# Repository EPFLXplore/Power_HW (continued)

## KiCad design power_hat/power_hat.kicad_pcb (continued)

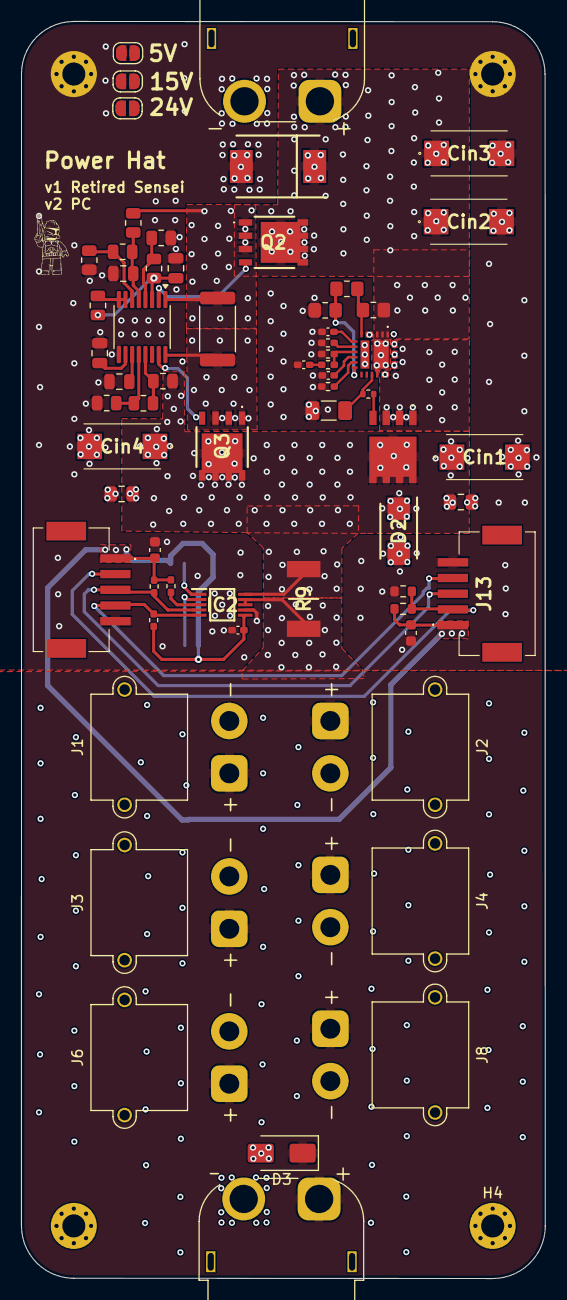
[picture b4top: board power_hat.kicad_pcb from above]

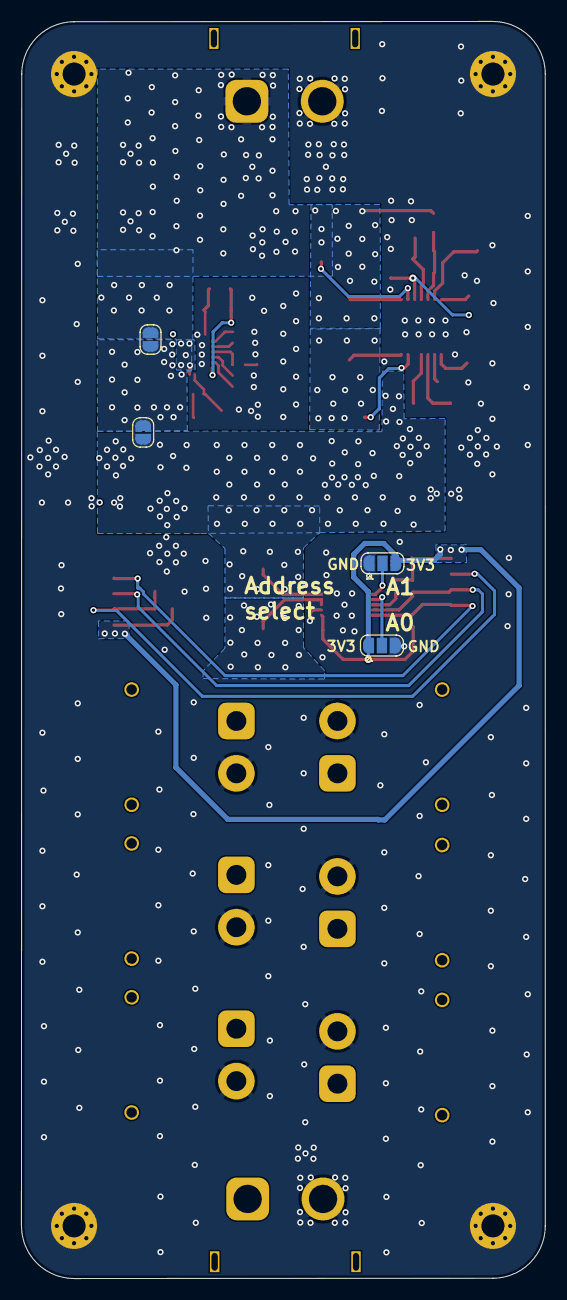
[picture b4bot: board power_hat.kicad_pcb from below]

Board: 4 copper layers, 50.0 x 120.0 mm, 71 parts (4 on the bottom side), 35 nets.

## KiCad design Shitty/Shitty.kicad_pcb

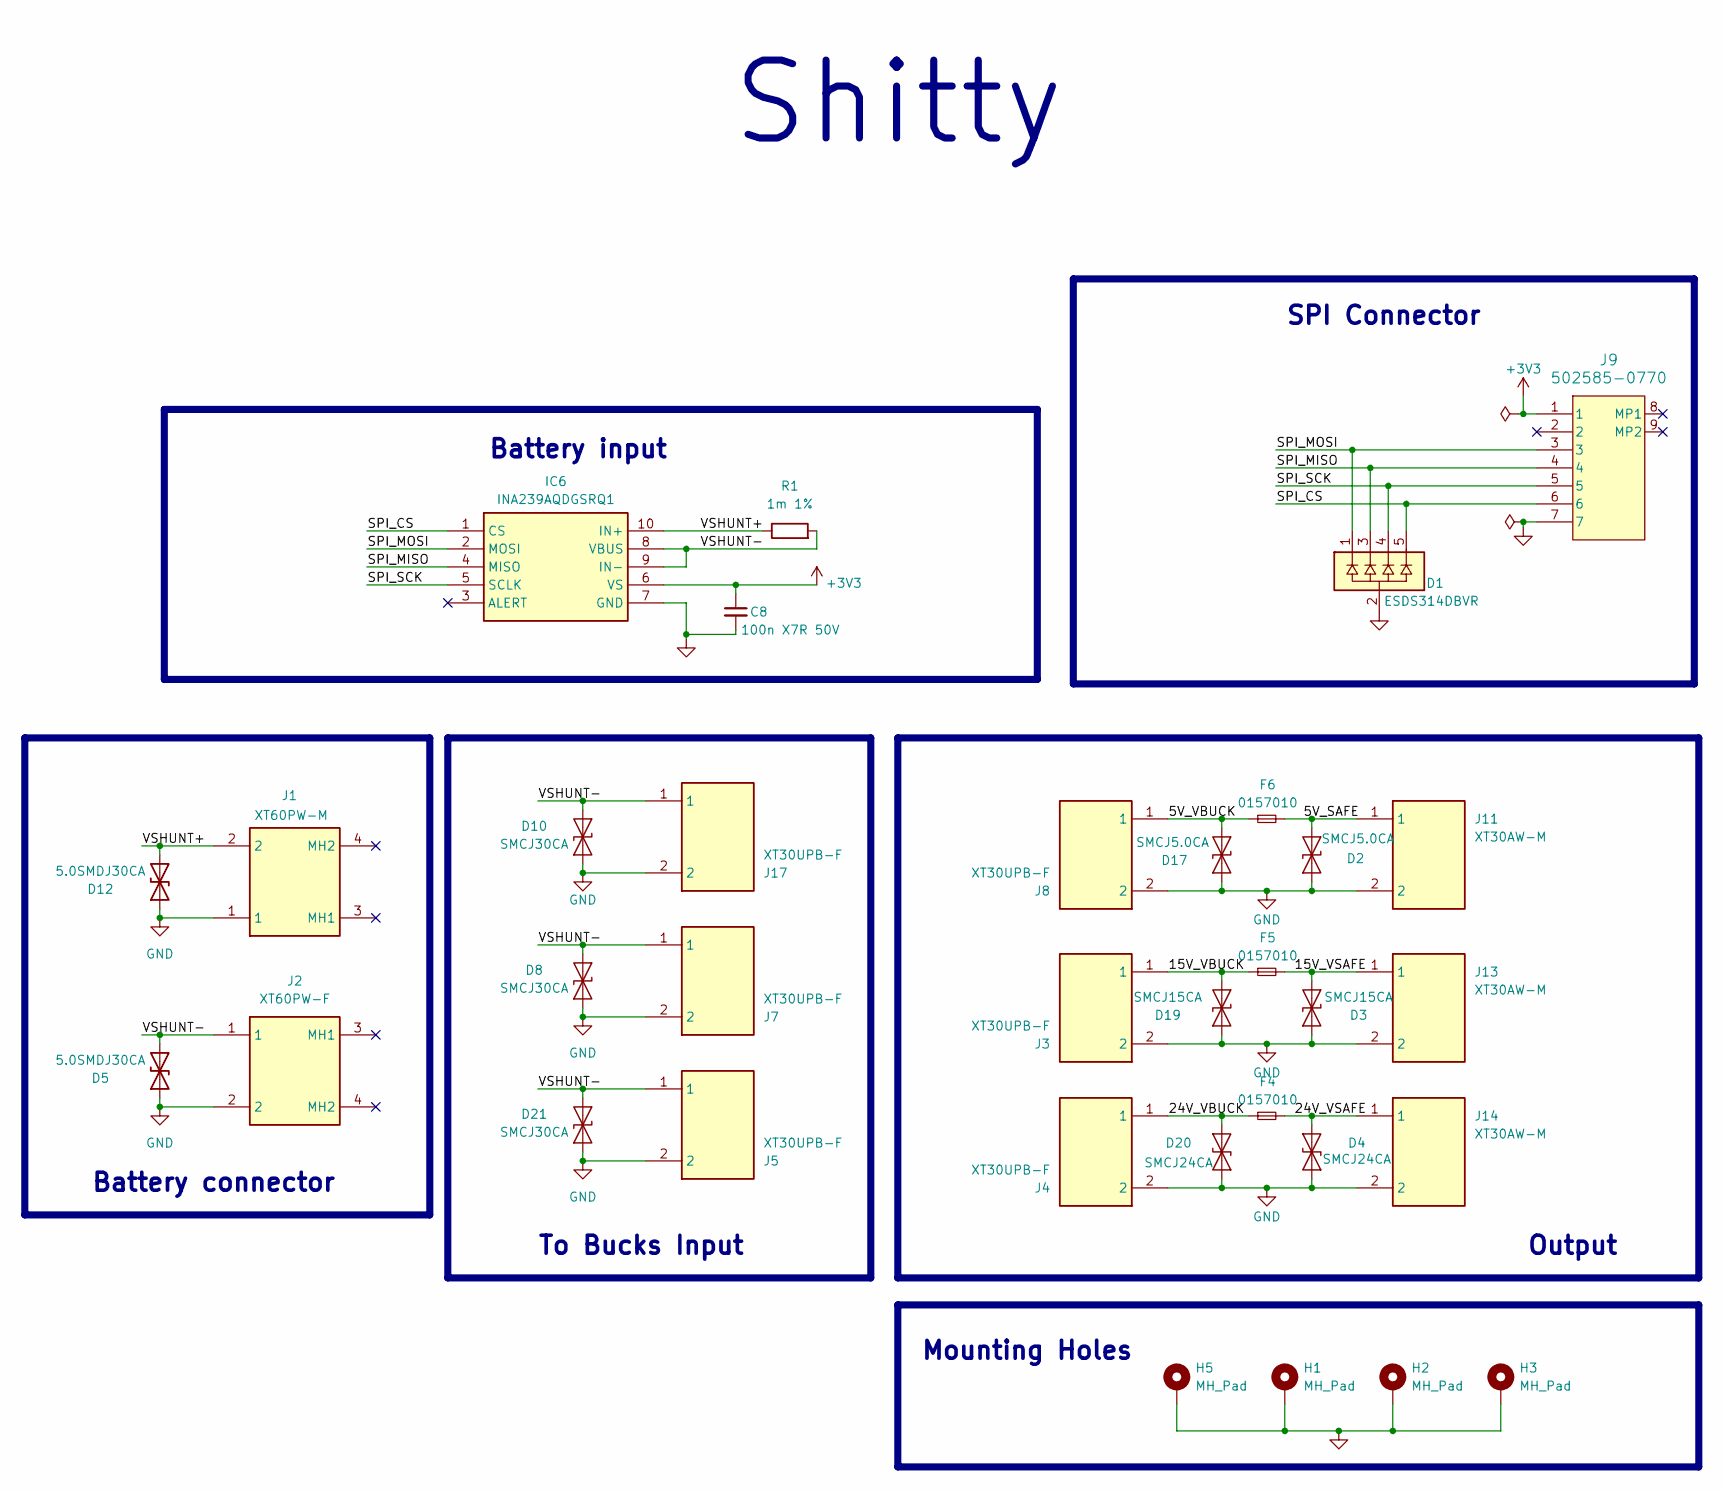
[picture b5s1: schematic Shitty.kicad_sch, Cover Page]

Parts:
C8: 100n X7R 50V; C_0603_1608Metric; Manufacturer Part Number GCM155R71H104KE02J
D1: ESDS314DBVR; SOT95P280X145-5N; Mouser Part Number 595-ESDS314DBVR
D2, D17: SMCJ5.0CA; D_SMA; Mouser Part Number 576-SMCJ5.0CA
D3, D19: SMCJ15CA; D_SMA; Mouser Part Number 576-SMCJ15CA
D4, D20: SMCJ24CA; D_SMA; Mouser Part Number 576-SMCJ24CA
D5, D12: 5.0SMDJ30CA; DIONM7959X262N; Mouser Part Number 652-5.0SMDJ30CA
D8, D10, D21: SMCJ30CA; D_SMA; Mouser Part Number 576-SMCJ30CA
F4, F5, F6: 0157010; Fuseholder_Littelfuse_Nano2_157x
H1, H2, H3, H5: MH_Pad; MountingHole_2.2mm_M2_Pad_Via
IC6: INA239AQDGSRQ1; SOP50P490X110-10N; Mouser Part Number 595-INA239AQDGSRQ1
J1: XT60PW-M; XT60PWM; Manufacturer_Part_Number XT60PW-M
J2: XT60PW-F; XT60PWF; Manufacturer_Part_Number XT60PW-F
J3, J4, J5, J7, J8, J17: XT30UPB-F; XT30UPBF; Manufacturer_Part_Number XT30UPB-F
J9: 502585-0770; 5025850770; Manufacturer Part Number 502585-0770
J11, J13, J14: XT30AW-M; XT30AWM; Manufacturer_Part_Number XT30AW-M
R1: 1m 1%; WSL39211L000JEA

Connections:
+3V3: C8.1, IC6.6 (VS), J9.1
/5V_SAFE: D2.1 (A1), F6.2, J11.1
/5V_VBUCK: D17.1 (A1), F6.1, J8.1
/15V_VBUCK: D19.1 (A1), F5.1, J3.1
/15V_VSAFE: D3.1 (A1), F5.2, J13.1
/24V_VBUCK: D20.1 (A1), F4.1, J4.1
/24V_VSAFE: D4.1 (A1), F4.2, J14.1
/SPI_CS: D1.5, IC6.1 (CS), J9.6
/SPI_MISO: D1.3, IC6.4 (MISO), J9.4
/SPI_MOSI: D1.1, IC6.2 (MOSI), J9.3
/SPI_SCK: D1.4, IC6.5 (SCLK), J9.5
/VSHUNT+: D12.2 (A2), IC6.10 (IN+), J1.2, R1.1
/VSHUNT-: D5.2 (A2), D8.1 (A1), D10.1 (A1), D21.1 (A1), IC6.8 (VBUS), IC6.9 (IN-), J2.1, J5.1, J7.1, J17.1, R1.2
GND: C8.2, D1.2, D2.2 (A2), D3.2 (A2), D4.2 (A2), D5.1 (A1), D8.2 (A2), D10.2 (A2), D12.1 (A1), D17.2 (A2), D19.2 (A2), D20.2 (A2), D21.2 (A2), H1.1, H2.1, H3.1, H5.1, IC6.7 (GND), J1.1, J2.2, J3.2, J4.2, J5.2, J7.2, J8.2, J9.7, J11.2, J13.2, J14.2, J17.2

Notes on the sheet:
Shitty
Output
Battery connector
Mounting Holes
Battery input
To Bucks Input
SPI Connector

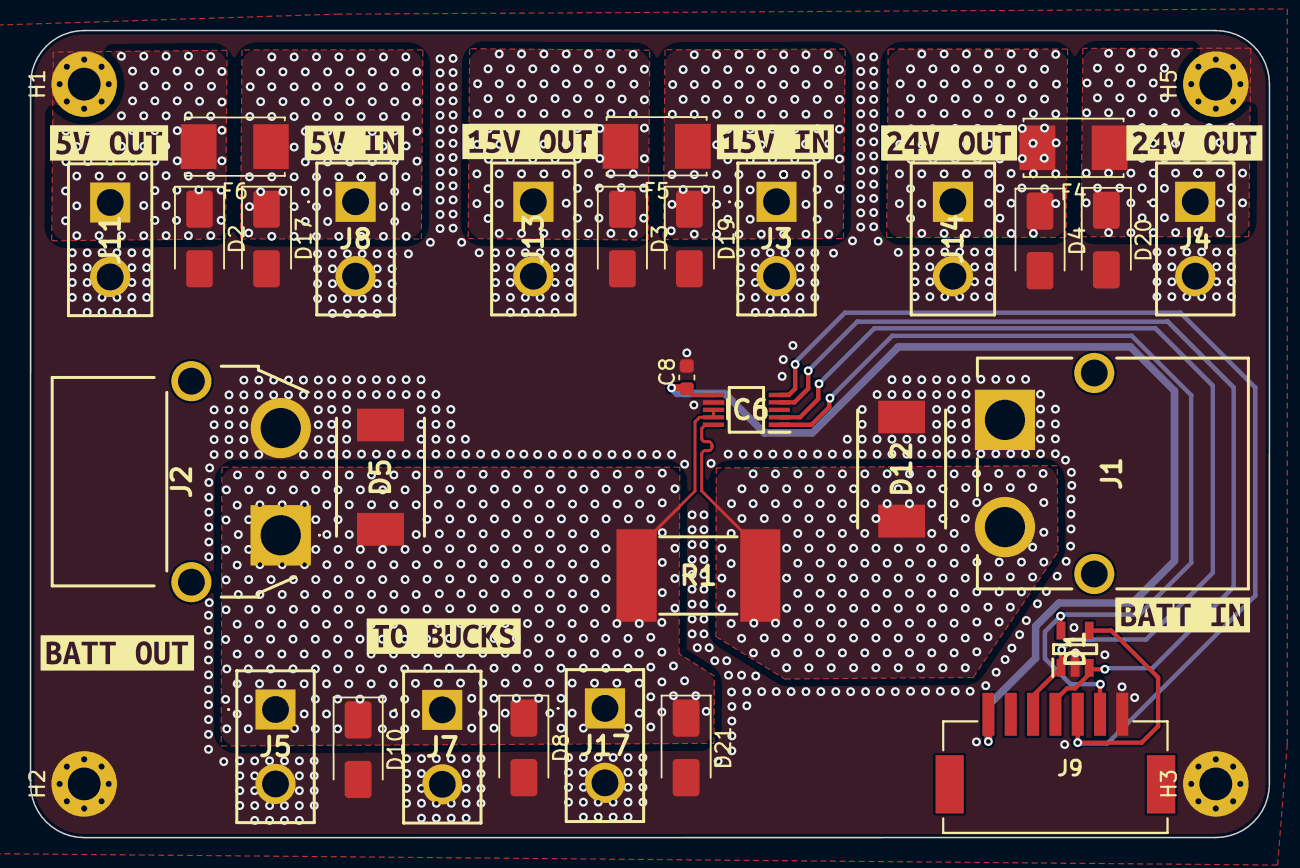
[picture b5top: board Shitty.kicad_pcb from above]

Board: 4 copper layers, 83.2 x 54.2 mm, 43 parts (0 on the bottom side), 14 nets.

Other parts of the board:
kibuzzard-69DD6D6A: G***; kibuzzard-69DD6D6A
kibuzzard-69DD6D60: G***; kibuzzard-69DD6D60
kibuzzard-69DD83D1: G***; kibuzzard-69DD83D1
kibuzzard-69DD83EE: G***; kibuzzard-69DD83EE
kibuzzard-69DD83F7: G***; kibuzzard-69DD83F7
kibuzzard-69DD712B: G***; kibuzzard-69DD712B
kibuzzard-69DD715C: G***; kibuzzard-69DD715C
kibuzzard-69DD7122: G***; kibuzzard-69DD7122
kibuzzard-69DD7155: G***; kibuzzard-69DD7155

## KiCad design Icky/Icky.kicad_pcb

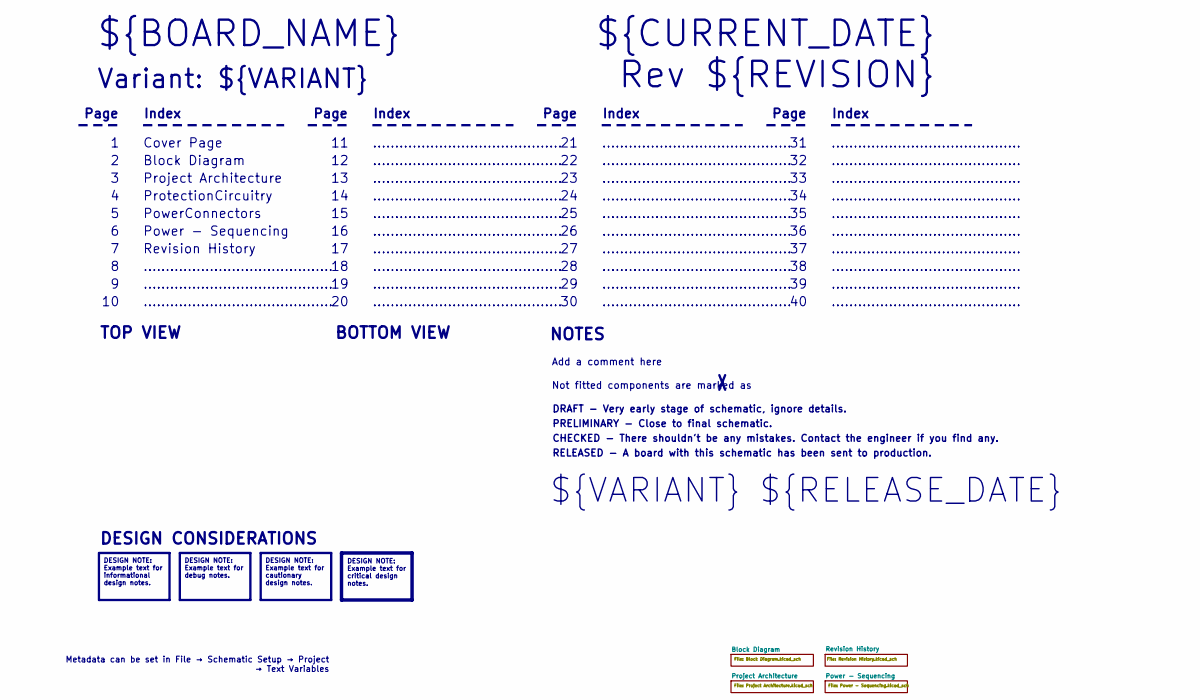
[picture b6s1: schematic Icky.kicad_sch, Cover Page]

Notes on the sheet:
BOTTOM VIEW
...........................................
RELEASED - A board with this schematic has been sent to production.
Page
TOP VIEW
Not fitted components are marked as
Index
PRELIMINARY - Close to final schematic.
${VARIANT} ${RELEASE_DATE}
ProtectionCircuitry
${CURRENT_DATE}
Variant: ${VARIANT}
Rev ${REVISION}
PowerConnectors
${BOARD_NAME}
DRAFT - Very early stage of schematic, ignore details.
Power - Sequencing
Block Diagram
Add a comment here
Cover Page
NOTES
Project Architecture
CHECKED - There shouldn't be any mistakes. Contact the engineer if you find any.
DESIGN CONSIDERATIONS
Revision History
Metadata can be set in File → Schematic Setup → Project → Text Variables
DESIGN NOTE: Example text for informational design notes.
DESIGN NOTE: Example text for cautionary design notes.
DESIGN NOTE: Example text for debug notes.
DESIGN NOTE: Example text for critical design notes.

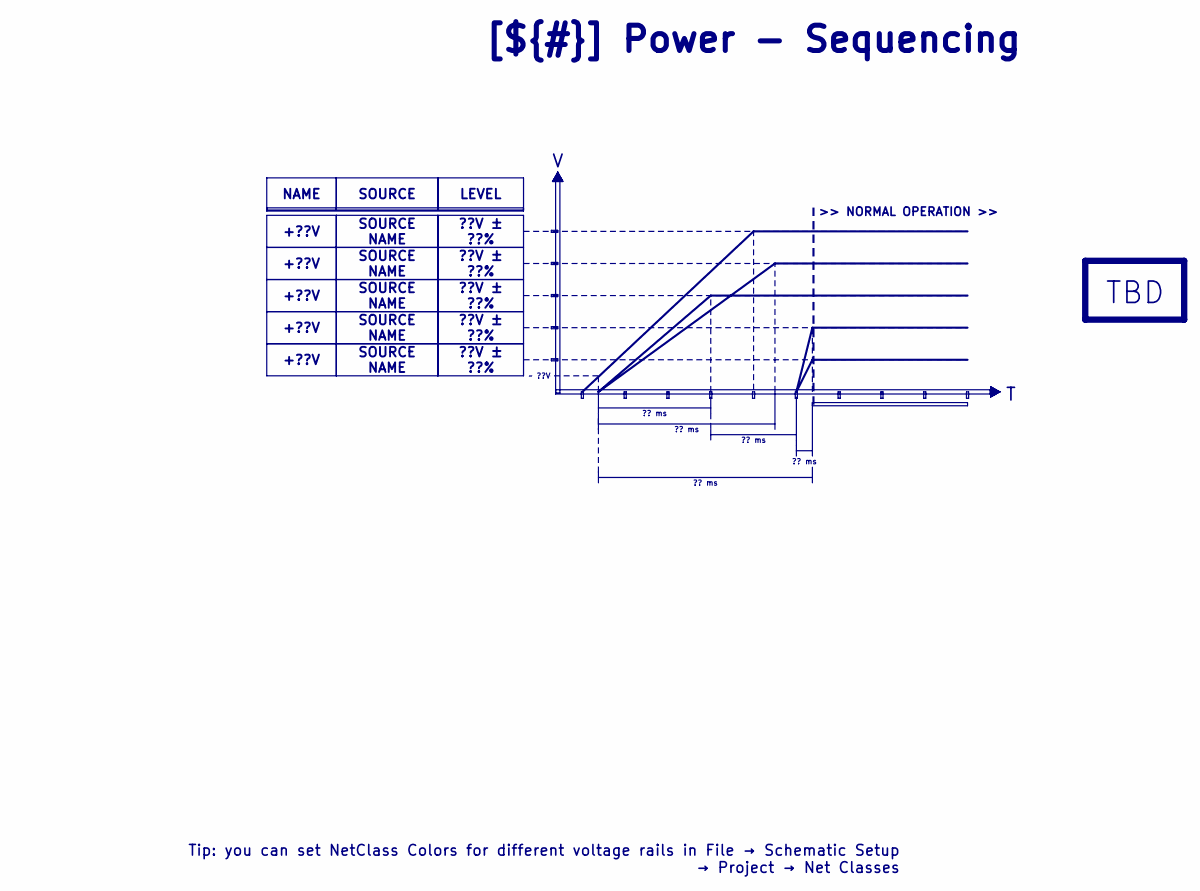
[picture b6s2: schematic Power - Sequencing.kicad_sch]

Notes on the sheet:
>> NORMAL OPERATION >>
LEVEL
+??V
SOURCE NAME
?? ms
??V ± ??%
[${#}] ${TITLE}
TBD
~ ??V
NAME
SOURCE
Tip: you can set NetClass Colors for different voltage rails in File → Schematic Setup → Project → Net Classes

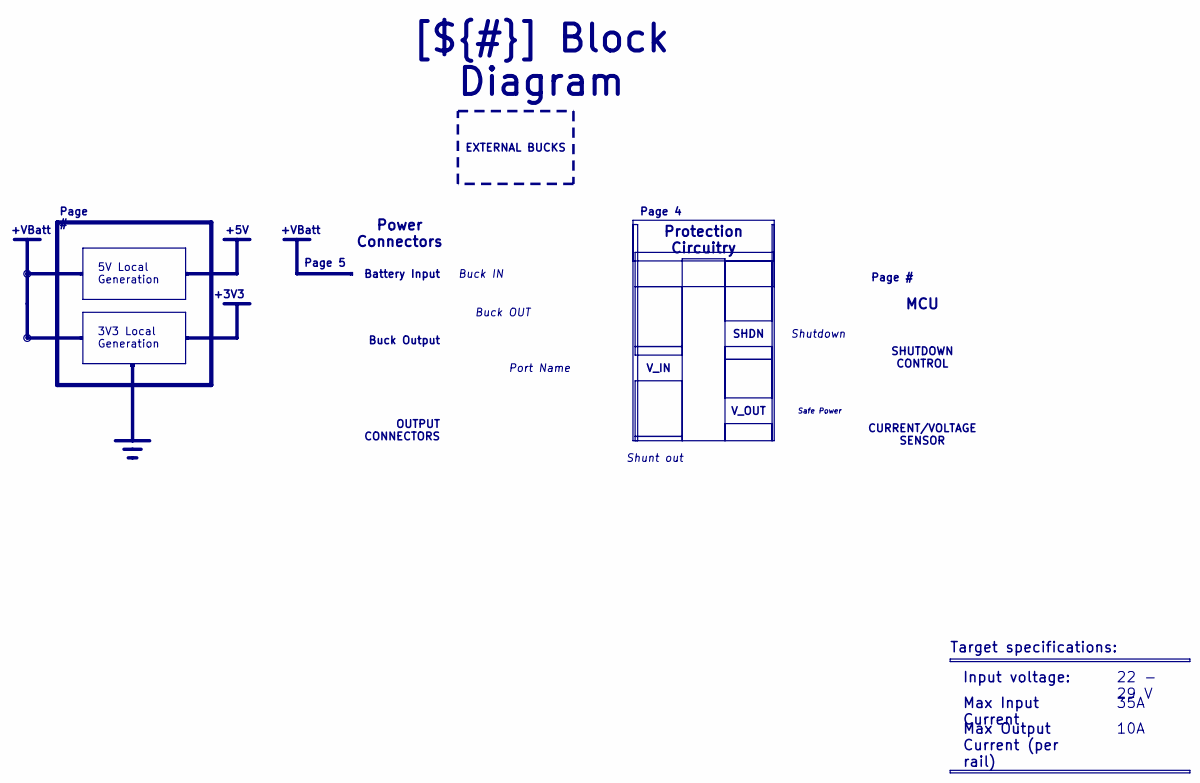
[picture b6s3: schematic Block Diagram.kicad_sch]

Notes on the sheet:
+5V
+3V3
+VBatt
Max Output Current (per rail)
3V3 Local Generation
EXTERNAL BUCKS
Max Input Current
Buck OUT
Protection Circuitry
Shunt out
V_IN
Page #
Shutdown
Input voltage:
Buck IN
35A
OUTPUT CONNECTORS
Safe Power
MCU
Battery Input
CURRENT/VOLTAGE SENSOR
SHUTDOWN CONTROL
[${#}] ${TITLE}
Target specifications:
10A
Page 5
Power Connectors
22 - 29 V
Page 4
V_OUT
Port Name
SHDN
Buck Output
5V Local Generation

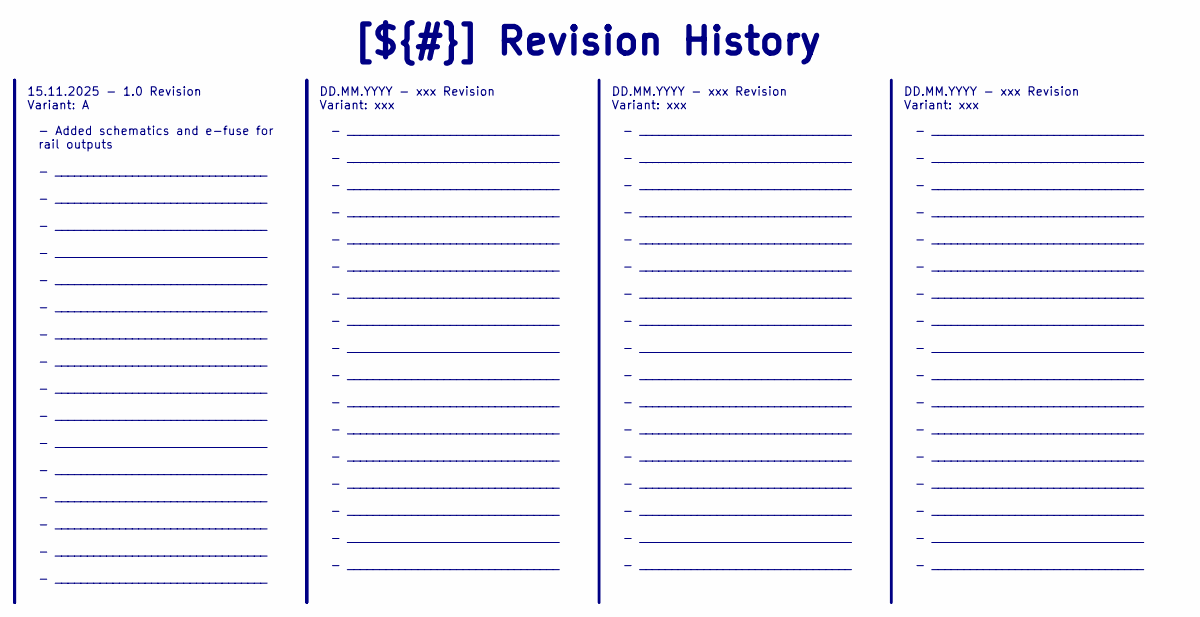
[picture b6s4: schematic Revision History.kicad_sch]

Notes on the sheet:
- _________________________________ - _________________________________ - _________________________________ - _________________________________ - _________________________________ - _________________________________ - _________________________________ - _________________________________ - _________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
DD.MM.YYYY - xxx Revision Variant: xxx
[${#}] ${TITLE}
- Added schematics and e-fuse for rail outputs - _________________________________ - _________________________________ - _________________________________ - _________________________________ - _________________________________ - _________________________________ - _________________________________ 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
15.11.2025 - 1.0 Revision Variant: A

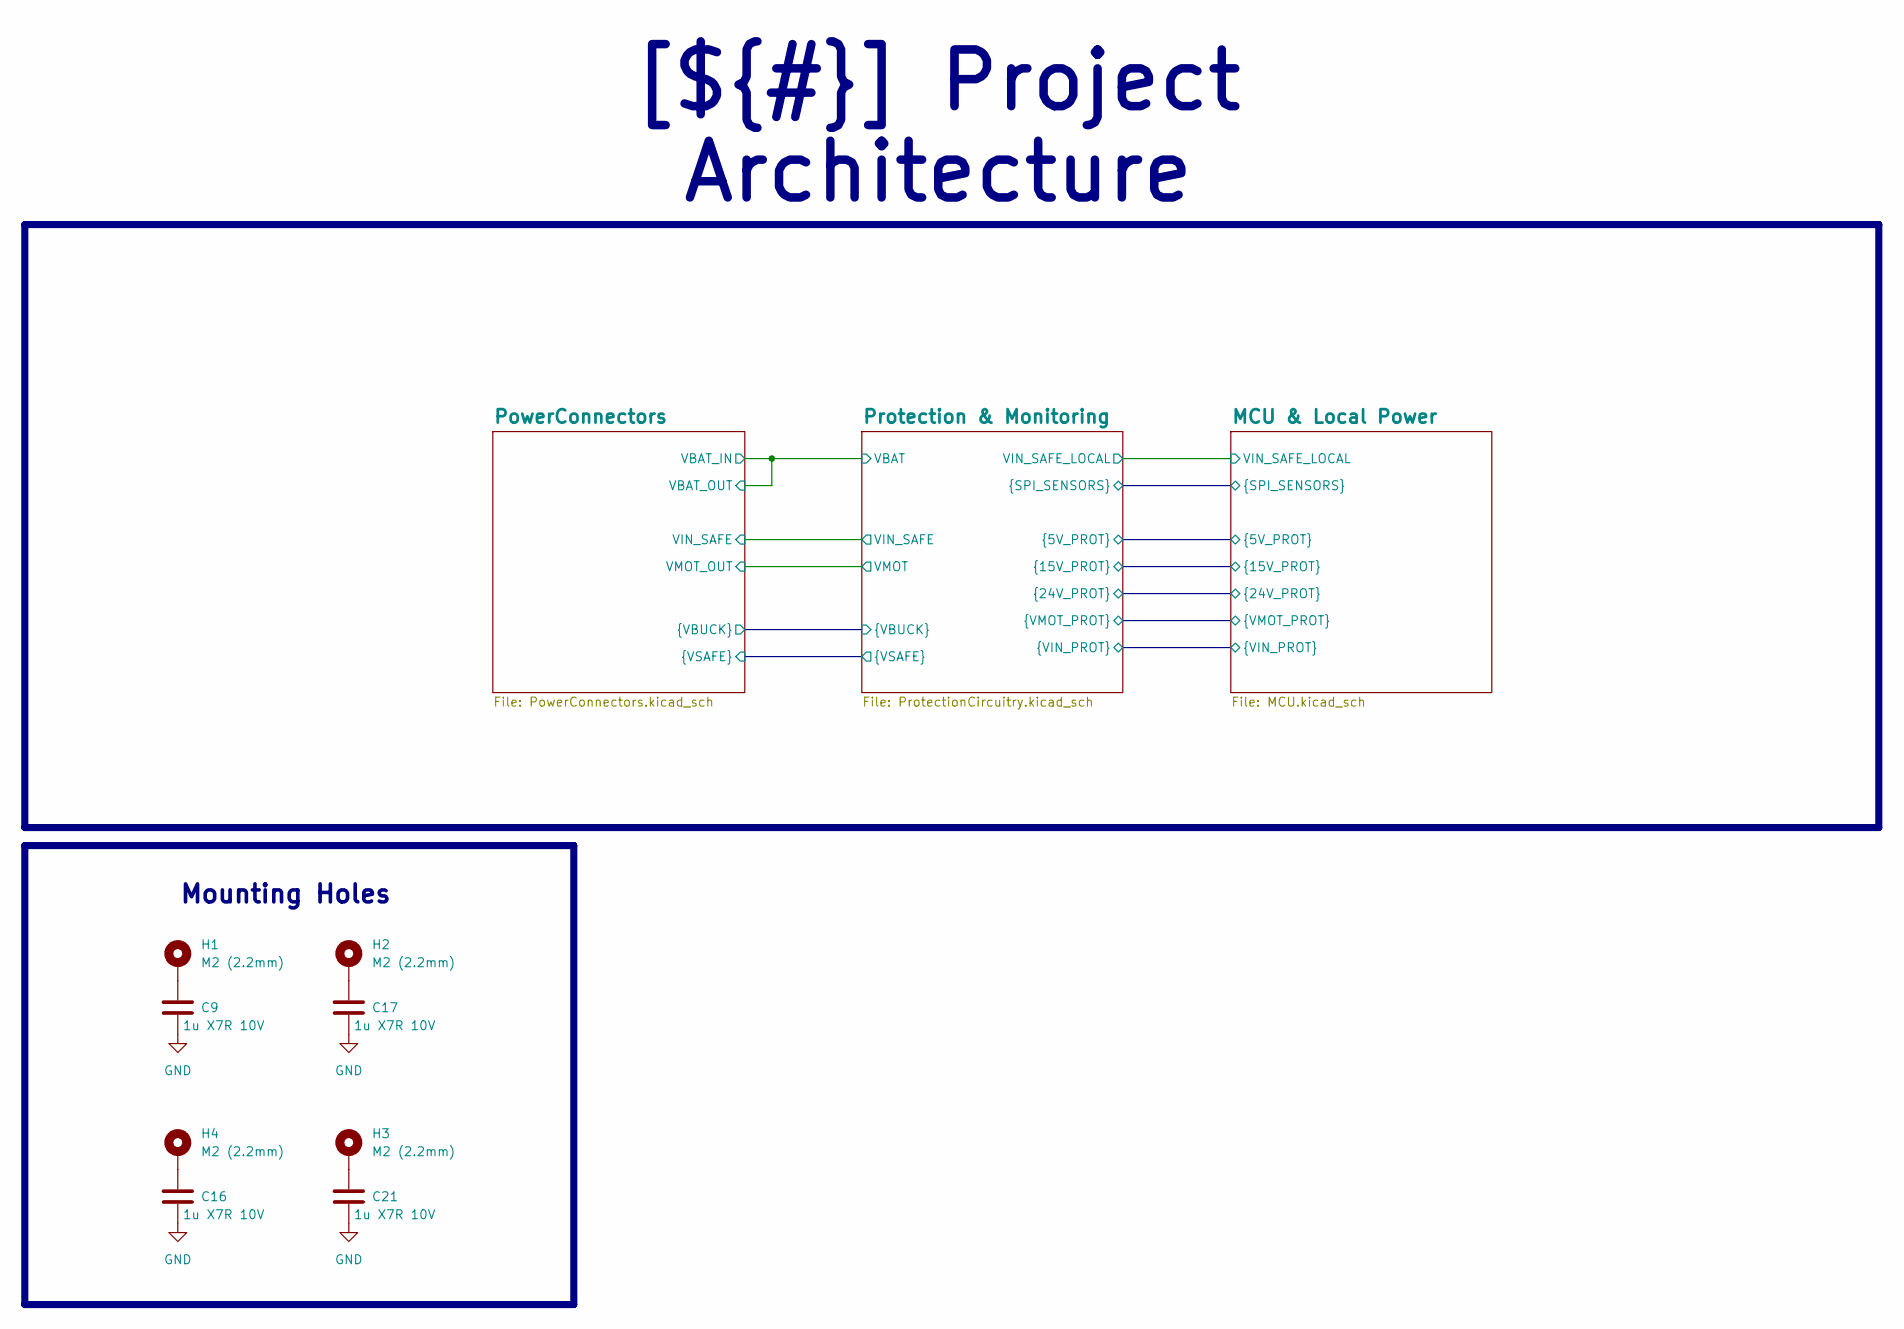
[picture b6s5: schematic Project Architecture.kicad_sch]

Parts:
C9, C16, C17, C21: 1u X7R 10V; C_0603_1608Metric; Manufacturer Part Number GRM155Z71A105KE01J
H1, H2, H3, H4: M2 (2.2mm); MountingHole_2.2mm_M2_Pad_Via

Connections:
unnamed: C9.1, H1.1
unnamed: C16.1, H4.1
unnamed: C17.1, H2.1
unnamed: C21.1, H3.1

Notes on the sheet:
Mounting Holes
[${#}] ${TITLE}

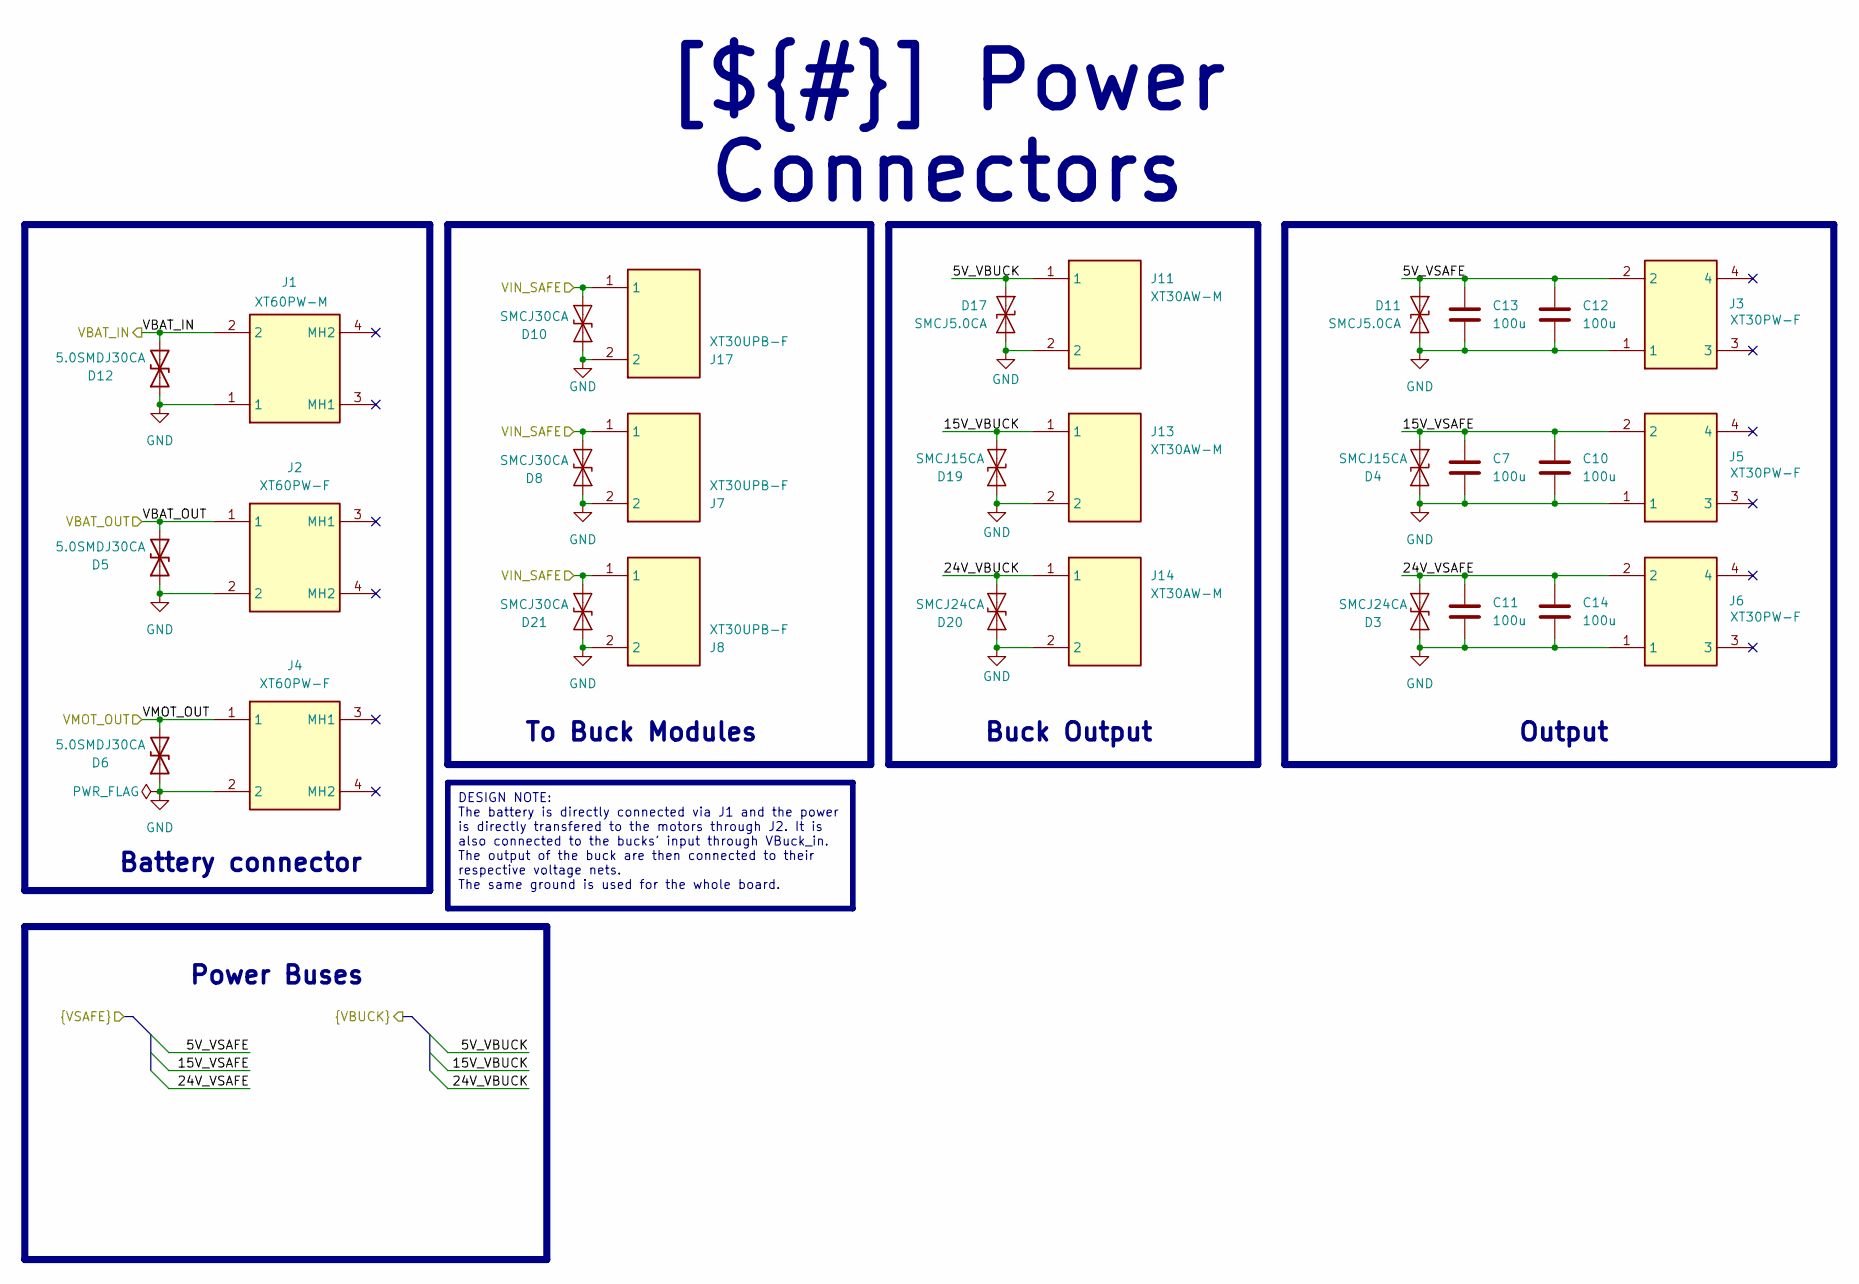
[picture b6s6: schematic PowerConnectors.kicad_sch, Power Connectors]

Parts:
C7, C10, C11, C12, C13, C14: 100u; C_1812_4532Metric_Pad1.57x3.40mm_HandSolder
D3, D20: SMCJ24CA; D_SMA; Mouser Part Number 576-SMCJ24CA
D4, D19: SMCJ15CA; D_SMA; Mouser Part Number 576-SMCJ15CA
D5, D6, D12: 5.0SMDJ30CA; DIONM7959X262N; Mouser Part Number 652-5.0SMDJ30CA
D8, D10, D21: SMCJ30CA; D_SMA; Mouser Part Number 576-SMCJ30CA
D11, D17: SMCJ5.0CA; D_SMA; Mouser Part Number 576-SMCJ5.0CA
J1: XT60PW-M; XT60PWM; Manufacturer_Part_Number XT60PW-M
J2, J4: XT60PW-F; XT60PWF; Manufacturer_Part_Number XT60PW-F
J3, J5, J6: XT30PW-F; XT30PWF; Manufacturer_Part_Number XT30PW-F
J7, J8, J17: XT30UPB-F; XT30UPBF; Manufacturer_Part_Number XT30UPB-F
J11, J13, J14: XT30AW-M; XT30AWM; Manufacturer_Part_Number XT30AW-M

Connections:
/Project Architecture/PowerConnectors/5V_VBUCK: D17.2 (A2), J11.1; also elsewhere on the board
/Project Architecture/PowerConnectors/15V_VBUCK: D19.1 (A1), J13.1; also elsewhere on the board
/Project Architecture/PowerConnectors/24V_VBUCK: D20.2 (A2), J14.1; also elsewhere on the board
VBAT: D5.2 (A2), D12.2 (A2), J1.2, J2.1; also elsewhere on the board

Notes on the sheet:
Battery connector
Output
To Buck Modules
DESIGN NOTE: The battery is directly connected via J1 and the power is directly transfered to the motors through J2. It is also connected to the bucks' input through VBuck_in. The output of the buck are then connected to their respective voltage nets. The same ground is used for the whole board.
Power Buses
Buck Output
[${#}] ${TITLE}
